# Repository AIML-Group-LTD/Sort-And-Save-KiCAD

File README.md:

# Sort-And-Save-KiCAD
Circuit schematic and PCB design for the Sort and Save scanner

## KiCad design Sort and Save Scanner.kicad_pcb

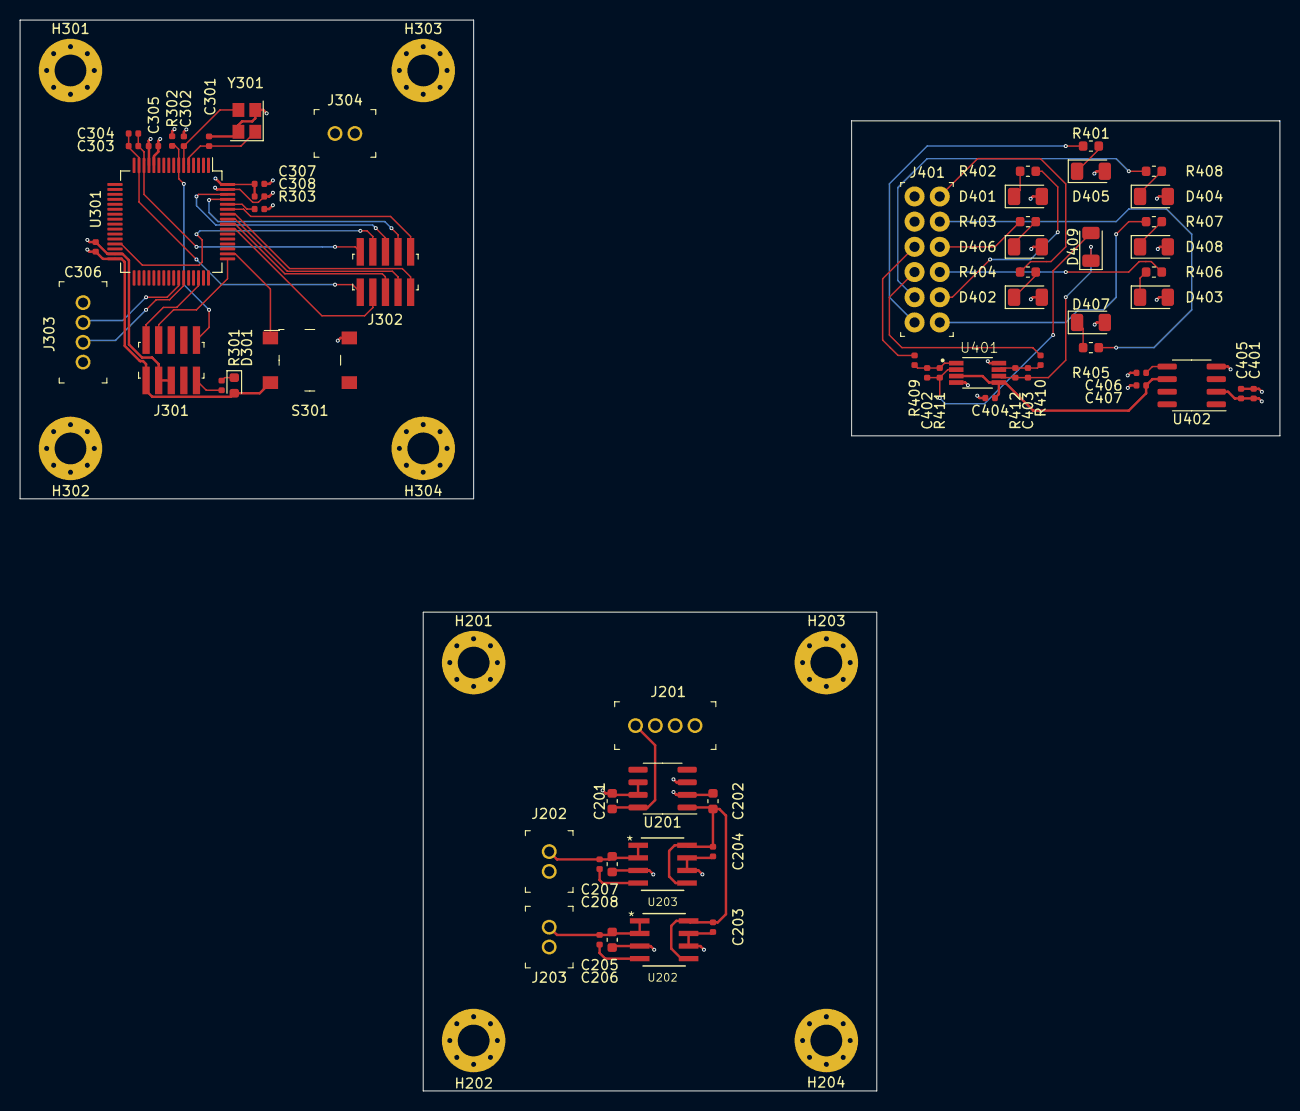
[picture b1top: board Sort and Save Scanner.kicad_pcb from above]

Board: 4 copper layers, 127.0 x 107.9 mm, 72 parts (0 on the bottom side), 52 nets.

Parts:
C201: 0.33uF; C_0603_1608Metric
C202: 0.01uF; C_0603_1608Metric
C203, C204, C305, C405, C406, C407: 1uF; C_0402_1005Metric
C205, C207: 10nf; C_0402_1005Metric
C206, C208: 10uF; C_0603_1608Metric
C301, C302: 10pF; C_0402_1005Metric
C303: 100pF; C_0402_1005Metric
C304: 47nF; C_0402_1005Metric
C306, C307, C308, C401, C404: 100nF; C_0402_1005Metric
C402, C403: 51pF; C_0402_1005Metric
D301: Green; LED_0603_1608Metric
D401: 850nm; LED_1206_3216Metric
D402: 1050nm; LED_1206_3216Metric
D403: 1300nm; LED_1206_3216Metric
D404: 1650nm; LED_1206_3216Metric
D405: White; LED_1206_3216Metric
D406: 940nm; LED_1206_3216Metric
D407: 1200nm; LED_1206_3216Metric
D408: 1450nm; LED_1206_3216Metric
D409: SD003-151; LED_1206_3216Metric
H201, H202, H203, H204, H301, H302, H303, H304: MountingHole_Pad; MountingHole_3.2mm_M3_Pad_Via
J201, J303: B4B-PH-K-S_LF__SN_; PinHeader_1x4_P2mm_Drill1mm
J202, J203, J304: B2B-PH-K-S_LF__SN_; PinHeader_1x2_P2mm_Drill1mm
J301, J302: FTSH-105-01-F-DV-K; PinHeader_2x5_P1.27_SMD
J401: 67996-412HLF; PinHeader_6x2_P2.54mm_Vertical
R301: 1K; R_0402_1005Metric
R302, R303: 100k; R_0402_1005Metric
R401, R406, R408: 51; R_0603_1608Metric
R402: 66; R_0603_1608Metric
R403: 27; R_0603_1608Metric
R404: 43; R_0603_1608Metric
R405, R407: 47; R_0603_1608Metric
R409, R410: 301; R_0402_1005Metric
R411, R412: 240k; R_0402_1005Metric
S301: Scan_Button; Switch_Tactile_SMD_6x6mm_PTS645
U201: LM78L12_SO8; SOIC-8_3.9x4.9mm_P1.27mm
U202: LT1763CS8-5; SO-8_S
U203: LT1763CS8-3.3; SO-8_S
U301: STM32F051R8Tx; LQFP-64_10x10mm_P0.5mm
U401: OPA2376AIDR-8; SOP65P490X110-8N
U402: REF5025AD; SOIC-8_3.9x4.9mm_P1.27mm
Y301: 8MHz; Crystal_SMD_3225-4Pin_3.2x2.5mm

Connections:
+2V5: C404.2, C407.1, U401.3, U401.5, U402.6
+3V3: C207.1, C208.2, C305.1, C306.1, C307.1, C308.1, D301.2, J202.1, J301.1, J303.4, J304.1, R302.2, S301.3, U203.1, U203.2, U301.13, U301.32, U301.64
+5V: C205.1, C206.2, C401.2, C405.1, J203.1, J401.2, U202.1, U202.2, U401.8, U402.2
+12V: C202.2, C203.1, C204.1, U201.1, U202.5, U202.8, U203.5, U203.8
+24V: C201.2, J201.1, U201.8
/ARM Board/ANALOG_IN1: C303.1, C304.1, J302.2, U301.14
/ARM Board/ANALOG_IN2: C303.2, C304.2, J302.1, U301.15
/ARM Board/HSE_IN: C301.1, U301.5, Y301.1
/ARM Board/HSE_OUT: C302.1, U301.6, Y301.3
/ARM Board/LED_OUT1: J302.3, U301.55
/ARM Board/LED_OUT2: J302.5, U301.56
/ARM Board/LED_OUT3: J302.7, U301.57
/ARM Board/LED_OUT4: J302.9, U301.58
/ARM Board/LED_OUT5: J302.10, U301.59
/ARM Board/LED_OUT6: J302.8, U301.61
/ARM Board/LED_OUT7: J302.6, U301.62
/ARM Board/LED_OUT8: J302.4, U301.29
/ARM Board/NRST: J301.10, R302.1, U301.7
/ARM Board/SWCLK: J301.4, U301.49
/ARM Board/SWDIO: J301.2, U301.46
/ARM Board/UART_RX: J303.3, U301.42
/ARM Board/UART_TX: J303.2, U301.43
/Sensor/ANALOG_OUT1: J401.3, R409.2
/Sensor/ANALOG_OUT2: J401.4, R410.2
/Sensor/LED_PWR_IN1: J401.5, R408.2
/Sensor/LED_PWR_IN2: J401.7, R407.2
/Sensor/LED_PWR_IN3: J401.9, R406.2
/Sensor/LED_PWR_IN4: J401.11, R405.2
/Sensor/LED_PWR_IN5: J401.12, R404.2
/Sensor/LED_PWR_IN6: J401.10, R403.2
/Sensor/LED_PWR_IN7: J401.8, R402.2
/Sensor/LED_PWR_IN8: J401.6, R401.2
GND: C201.1, C202.1, C203.2, C204.2, C206.1, C208.1, C301.2, C302.2, C305.2, C306.2, C307.2, C308.2, C401.1, C404.1, C405.2, C406.2, C407.2, D401.2, D402.2, D403.2, D404.2, D405.2, D406.2, D407.2, D408.2, H201.1, H202.1, H203.1, H204.1, H301.1, H302.1, H303.1, H304.1, J201.4, J202.2, J203.2, J301.3, J301.5, J303.1, J304.2, J401.1, R303.2, S301.2, U201.2, U201.3, U201.6, U201.7, U202.3, U202.6, U202.7, U203.3, U203.6, U203.7, U301.12, U301.31, U301.63, U401.4, U402.4, Y301.2, Y301.4
unnamed: C205.2, U202.4
unnamed: C207.2, U203.4
unnamed: C402.1, D409.2, R411.1, U401.2
unnamed: C402.2, R409.1, R411.2, U401.1
unnamed: C403.1, D409.1, R412.1, U401.6
unnamed: C403.2, R410.1, R412.2, U401.7
unnamed: C406.1, U402.5
unnamed: D301.1, R301.2
unnamed: D401.1, R402.1
unnamed: D402.1, R404.1
unnamed: D403.1, R406.1
unnamed: D404.1, R408.1
unnamed: D405.1, R401.1
unnamed: D406.1, R403.1
unnamed: D407.1, R405.1
unnamed: D408.1, R407.1
unnamed: J301.9, R301.1
unnamed: R303.1, U301.60
unnamed: S301.1, U301.50

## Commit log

2021-01-20 v1.0.0
2021-01-22 Added STEP file
